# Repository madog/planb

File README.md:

# planb

Electrical and mechanical designs based on the Plan B powder printer (https://ytec3d.com/plan-b/)

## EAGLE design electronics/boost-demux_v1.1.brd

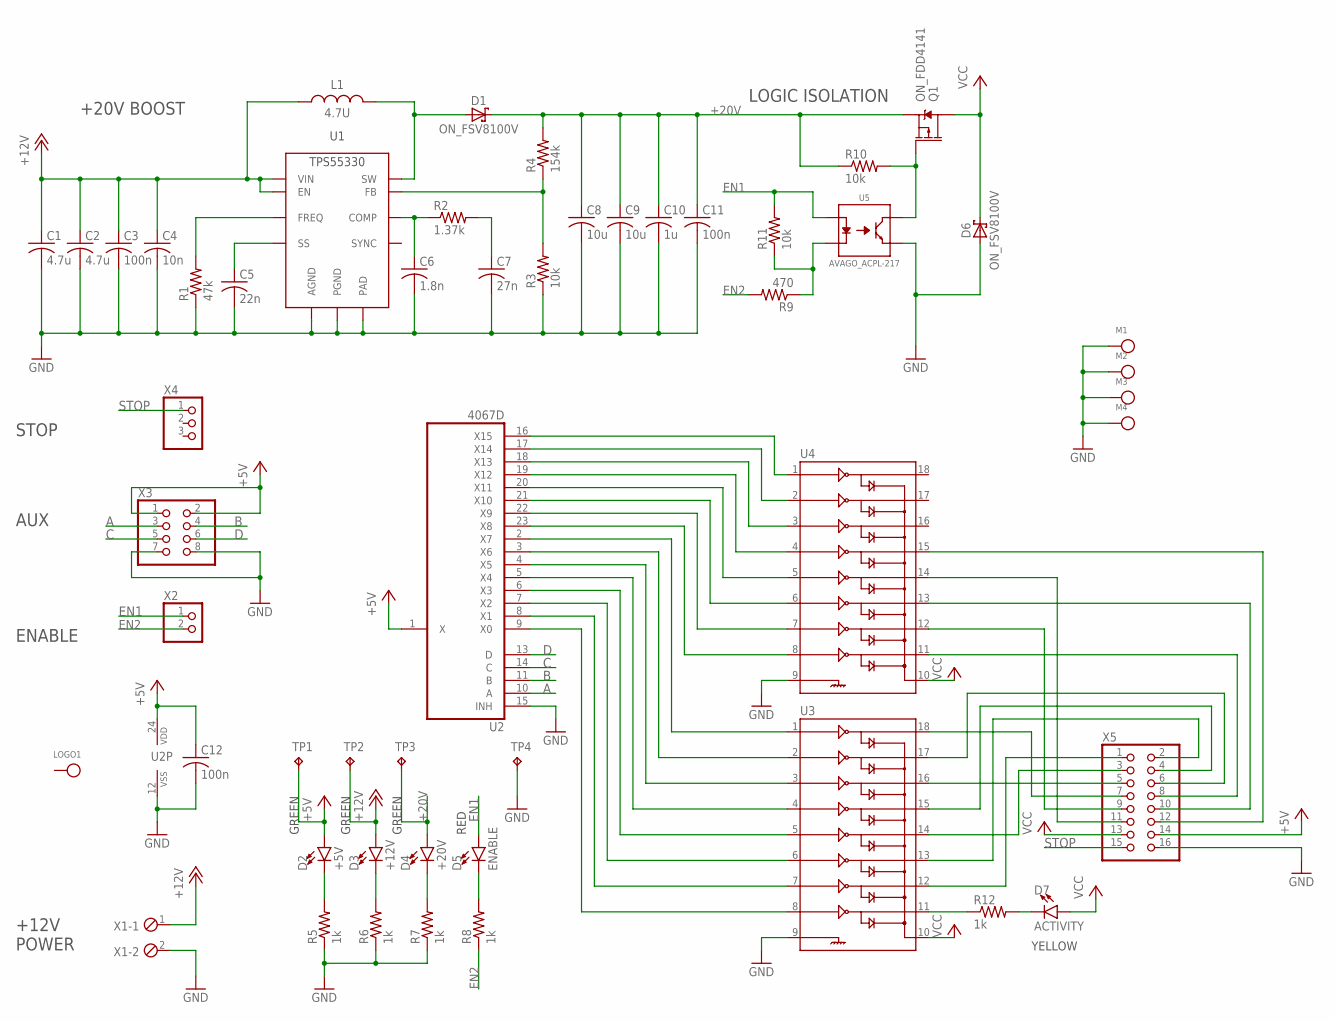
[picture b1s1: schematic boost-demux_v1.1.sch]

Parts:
C1, C2: 4.7u; C1206
C3, C11, C12: 100n; C1206
C4: 10n; C1206
C5: 22n; C1206
C6: 1.8n; C0805
C7: 27n; C0805
C8, C9: 10u; C1206
C10: 1u; C1206
D1, D6: ON_FSV8100V; TO-277-3
D2: +5V; LED_5MM
D3: +12V; LED_5MM
D4: +20V; LED_5MM
D5: ENABLE; LED_5MM
D7: ACTIVITY; LED_5MM
L1: 4.7U; 4440
LOGO1: MADOG
M1, M2, M3, M4: 6-32_MOUNT
Q1: ON_FDD4141; TO-252-3
R1: 47k; R1206
R2: 1.37k; R0805
R3, R10, R11: 10k; R0805
R4: 154k; R0805
R5, R6, R7, R8, R12: 1k; R1206
R9: 470; R1206
TP1, TP2, TP3, TP4: TPB1,27; B1,27
U1: TI_TPS55330; S-PWQFN-N16
U2: 4067D; SO24W
U3, U4: ULN2803SOICW; SO18L
U5: AVAGO_ACPL-217; SOIC-4
X1: MPT2; 2POL254
X2: PINHD-1X2/90; 1X02/90
X3: PINHD-2X4/90; 2X04/90
X4: PINHD-1X3/90; 1X03/90
X5: PINHD-2X8; 2X08

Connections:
+5V: C12.1, D2.A, TP1.TP, U2.1 (X), U2.24 (VDD), X3.1, X3.2, X5.14
+12V: C1.1, C2.1, C3.1, C4.1, D3.A, L1.1, TP2.TP, U1.2 (VIN), U1.3 (EN), X1.1
+20V: C8.1, C9.1, C10.1, C11.1, D1.P$3 (C), D4.A, Q1.P$3 (S), R4.2, R10.1, TP3.TP
A: U2.10 (A), X3.3
B: U2.11 (B), X3.4
C: U2.14 (C), X3.5
D: U2.13 (D), X3.6
EN1: D5.A, R11.2, U5.P$1, X2.1
EN2: R8.1, R9.2, X2.2
GND: C1.2, C2.2, C3.2, C4.2, C5.2, C6.2, C7.2, C8.2, C9.2, C10.2, C11.2, C12.2, D6.P$1 (A), D6.P$2 (A), M1.P$1, M1.P$2, M1.P$3, M1.P$4, M1.P$5, M1.P$6, M1.P$7, M1.P$8, M1.P$9, M2.P$1, M2.P$2, M2.P$3, M2.P$4, M2.P$5, M2.P$6, M2.P$7, M2.P$8, M2.P$9, M3.P$1, M3.P$2, M3.P$3, M3.P$4, M3.P$5, M3.P$6, M3.P$7, M3.P$8, M3.P$9, M4.P$1, M4.P$2, M4.P$3, M4.P$4, M4.P$5, M4.P$6, M4.P$7, M4.P$8, M4.P$9, R1.1, R3.1, R5.1, R6.1, R7.1, TP4.TP, U1.6 (AGND), U1.11 (PGND), U1.12 (PGND), U1.13 (PGND), U1.PAD, U2.12 (VSS), U2.15 (INH), U3.9, U4.9, U5.P$3, X1.2, X3.7, X3.8, X5.16
unnamed: R1.2, U1.9 (FREQ)
unnamed: C5.1, U1.4 (SS)
unnamed: C6.1, R2.1, U1.7 (COMP)
unnamed: C7.1, R2.2
unnamed: R3.2, R4.1, U1.8 (FB)
unnamed: D2.K (C), R5.2
unnamed: D1.P$1 (A), D1.P$2 (A), L1.2, U1.1 (SW), U1.15 (SW), U1.16 (SW)
unnamed: D3.K (C), R6.2
unnamed: D4.K (C), R7.2
unnamed: D5.K (C), R8.2
unnamed: U2.9 (X0), U3.8
unnamed: R12.1, U3.11
unnamed: Q1.P$1 (G), R10.2, U5.P$4
unnamed: U3.12, X5.1
unnamed: U2.8 (X1), U3.7
unnamed: U2.7 (X2), U3.6
unnamed: U2.6 (X3), U3.5
unnamed: U3.13, X5.2
unnamed: R9.1, R11.1, U5.P$2
unnamed: U2.5 (X4), U3.4
unnamed: U2.4 (X5), U3.3
unnamed: U2.3 (X6), U3.2
unnamed: U2.2 (X7), U3.1
unnamed: U2.23 (X8), U4.8
unnamed: U2.22 (X9), U4.7
unnamed: U2.21 (X10), U4.6
unnamed: U2.20 (X11), U4.5
unnamed: U2.19 (X12), U4.4
unnamed: U2.18 (X13), U4.3
unnamed: U2.17 (X14), U4.2
unnamed: U2.16 (X15), U4.1
unnamed: U3.14, X5.3
unnamed: U3.15, X5.4
unnamed: U3.16, X5.5
unnamed: U3.17, X5.6
unnamed: U3.18, X5.7
unnamed: U4.11, X5.8
unnamed: U4.12, X5.9
unnamed: U4.13, X5.10
unnamed: U4.14, X5.11
unnamed: U4.15, X5.12
unnamed: D7.K (C), R12.2
STOP: X4.1, X5.15
VCC: D6.P$3 (C), D7.A, Q1.P$4 (D), U3.10, U4.10, X5.13

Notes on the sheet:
+12V POWER
AUX
+20V BOOST
LOGIC ISOLATION
ENABLE
STOP
GREEN
RED
YELLOW

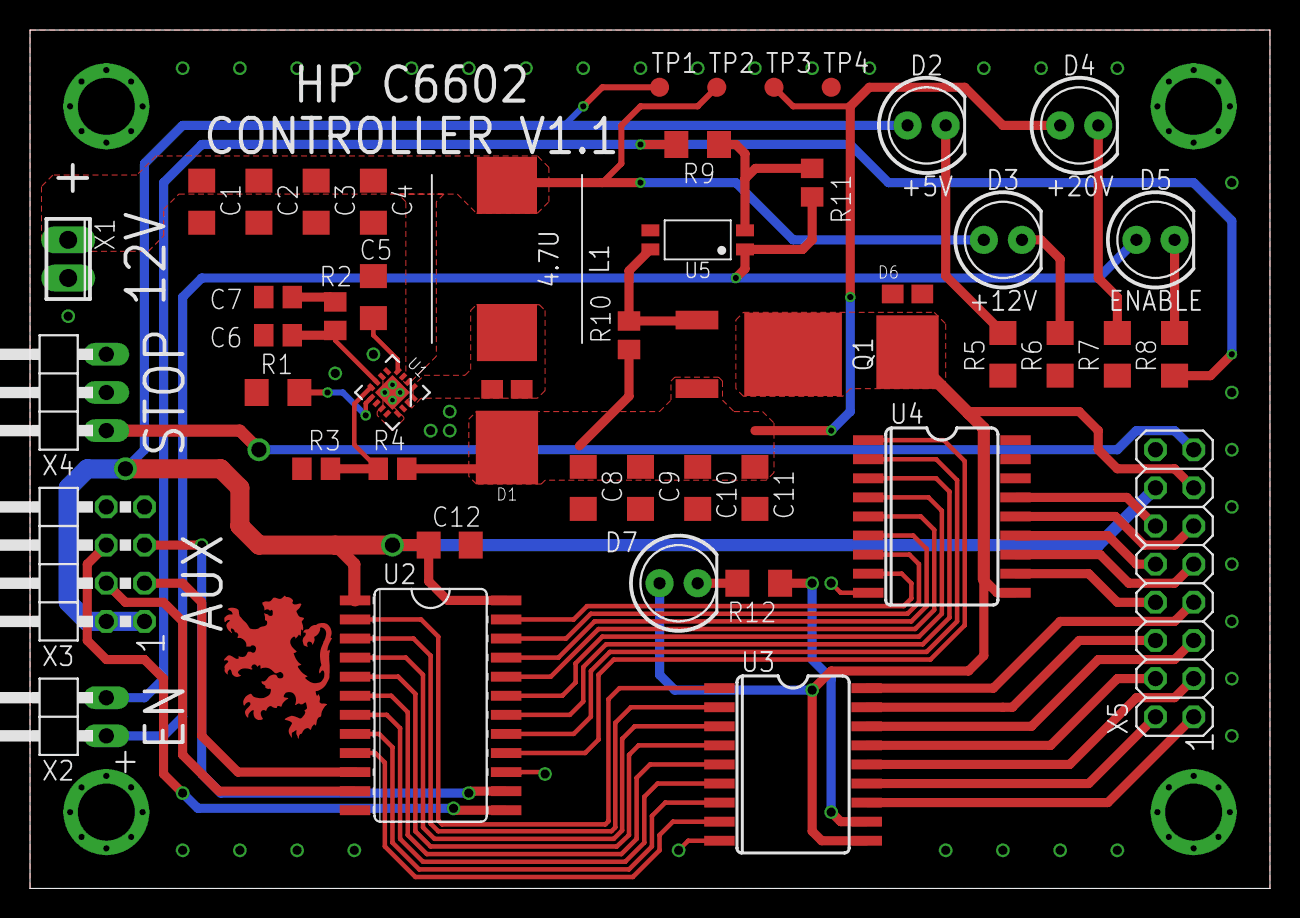
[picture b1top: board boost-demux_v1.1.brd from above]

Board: 2 copper layers, 82.5 x 57.1 mm, 52 parts (0 on the bottom side), 54 nets.

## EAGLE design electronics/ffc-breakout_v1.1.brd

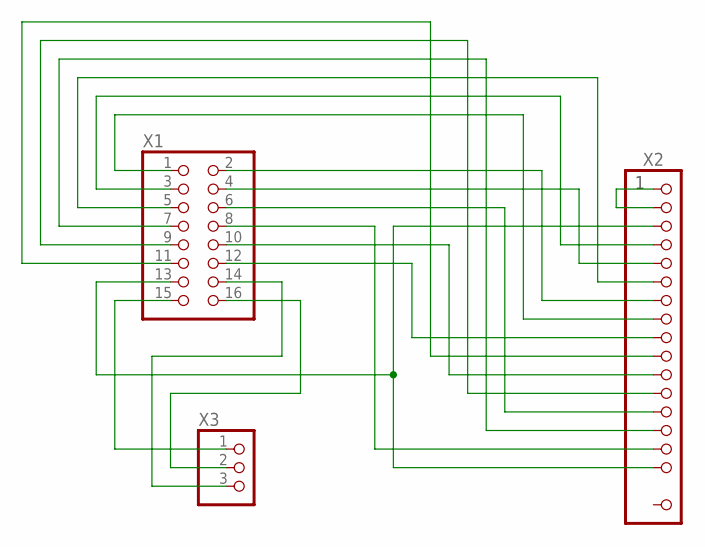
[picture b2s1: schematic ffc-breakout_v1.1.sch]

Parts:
X1: PINHD-2X8; 2X08
X2: AMP_SFW16R-2STE1LF
X3: PINHD-1X3/90; 1X03/90

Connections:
unnamed: X1.16, X3.2
unnamed: X1.15, X3.1
unnamed: X1.13, X2.P$3 (3), X2.P$16 (16)
unnamed: X1.14, X3.3
unnamed: X2.P$1 (1), X2.P$2 (2)
unnamed: X1.1, X2.P$8 (8)
unnamed: X1.2, X2.P$7 (7)
unnamed: X1.3, X2.P$4 (4)
unnamed: X1.4, X2.P$5 (5)
unnamed: X1.5, X2.P$6 (6)
unnamed: X1.6, X2.P$13 (13)
unnamed: X1.7, X2.P$14 (14)
unnamed: X1.8, X2.P$15 (15)
unnamed: X1.9, X2.P$12 (12)
unnamed: X1.10, X2.P$11 (11)
unnamed: X1.11, X2.P$10 (10)
unnamed: X1.12, X2.P$9 (9)

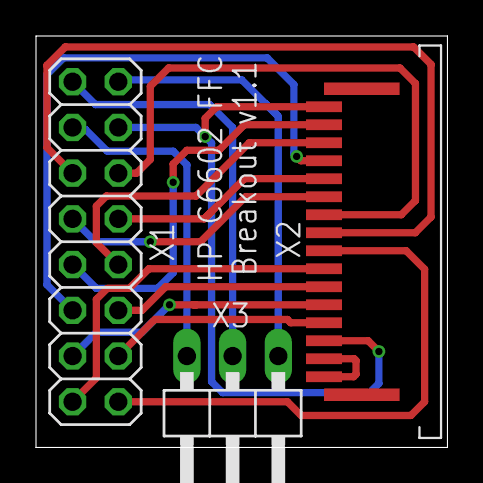
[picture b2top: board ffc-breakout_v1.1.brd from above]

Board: 2 copper layers, 22.9 x 22.9 mm, 3 parts (0 on the bottom side), 17 nets.

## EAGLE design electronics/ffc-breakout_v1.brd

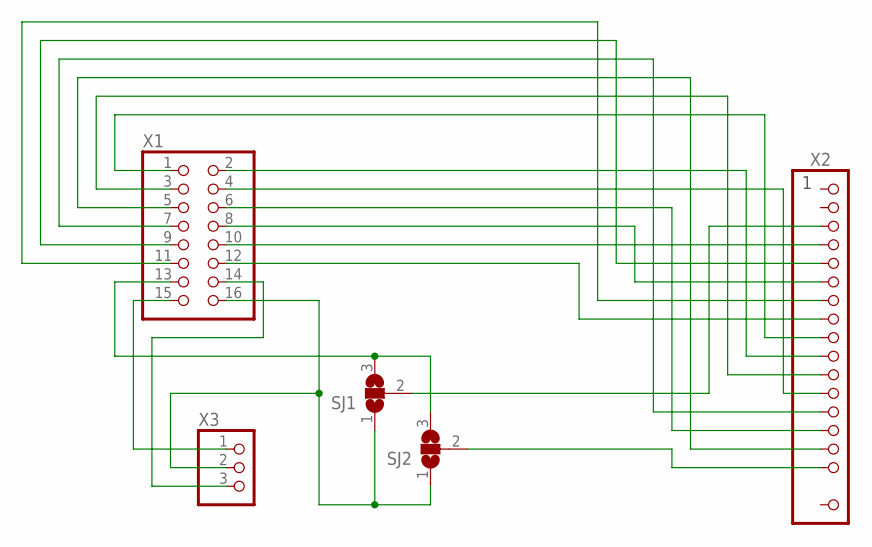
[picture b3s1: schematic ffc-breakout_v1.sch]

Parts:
SJ1, SJ2: SJ2W; SJ_2
X1: PINHD-2X8; 2X08
X2: AMP_SFW16R-2STE1LF
X3: PINHD-1X3/90; 1X03/90

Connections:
unnamed: SJ1.1, SJ2.1, X1.16, X3.2
unnamed: X1.15, X3.1
unnamed: SJ1.3, SJ2.3, X1.13
unnamed: X1.14, X3.3
unnamed: SJ1.2, X2.P$3 (3)
unnamed: X1.1, X2.P$9 (9)
unnamed: SJ2.2, X2.P$16 (16)
unnamed: X1.2, X2.P$10 (10)
unnamed: X1.3, X2.P$11 (11)
unnamed: X1.4, X2.P$12 (12)
unnamed: X1.5, X2.P$15 (15)
unnamed: X1.6, X2.P$14 (14)
unnamed: X1.7, X2.P$13 (13)
unnamed: X1.8, X2.P$6 (6)
unnamed: X1.9, X2.P$5 (5)
unnamed: X1.10, X2.P$4 (4)
unnamed: X1.11, X2.P$7 (7)
unnamed: X1.12, X2.P$8 (8)

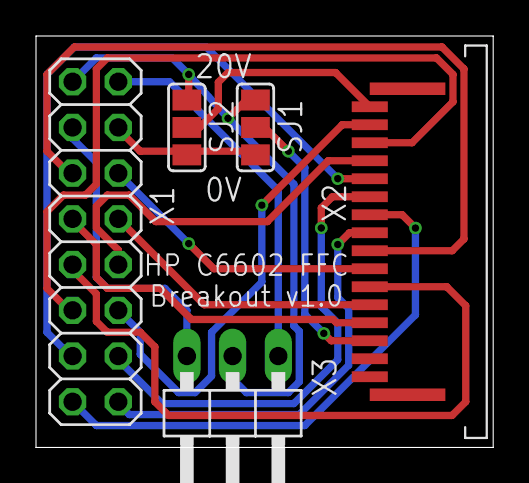
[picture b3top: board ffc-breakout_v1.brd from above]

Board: 2 copper layers, 25.4 x 22.9 mm, 5 parts (0 on the bottom side), 18 nets.

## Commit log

2017-08-27 Eagle project + schematic
2017-08-27 Add components lib + color palette
2017-08-27 Added Sparkfun libraries, OSHPark + DirtyPCBs files
2017-09-01 Components library - FFC connector (unfinished)
2017-09-02 Lib updates + boost-demux design
2017-09-03 Slight update to boost-demux schematic
2017-09-05 PCB draft less markup
2017-09-05 Added minor PCB markup
2017-09-06 Updates to boost-demux and FFC breakout
2017-09-06 FFC breakout autoroute
2017-09-06 FFC - much better autoroute + cleanup and markup
2017-09-06 DRC fixes
2017-09-06 BOM + minor FFC update
2017-09-08 Logos
2017-09-09 BOM updates and minor DRC fixes
2017-09-11 Rearrange + add mechanics and software files
2017-09-14 Removed Inventor files temporarily
2017-09-14 Updated all SW files to latest format
2017-09-14 Beginning of Inventor feature recognition
2017-09-14 Additional Inventor parts
2017-09-14 More parts + hardware
2017-09-14 More hardware
2017-09-15 Started sheet metal models
2017-09-15 Lots of parts
2017-09-15 Further parts
2017-09-17 Megatronics models
2017-09-17 Steppers
2017-09-17 Piston parts
2017-09-17 More piston parts
2017-09-18 Spreader parts +
2017-09-19 X-axis + Y-axis parts
2017-09-19 Subassemblies
2017-09-20 More subassembly
2017-09-22 Assemblies!
2017-09-25 Sheet metal mods
2017-09-25 Sheet metal drawings
2017-09-27 Hopper assy's
2017-09-27 More subassemblies + piston guide remodels
2017-09-28 Piston assy
2017-09-29 Finished subassys?
2017-10-03 Sheet metal updates + more assemblies
2017-10-03 Final subassemblies?
2017-10-05 Added STLs for 3D prints, moved Arduino source
2017-10-07 McMaster parts
2017-10-11 Parts list
2017-10-13 C6602 test program
2017-10-13 C6602 test draft
2017-10-13 Fixed test program bugs
2017-10-16 Test programs
2017-10-16 Pump test program update
2017-10-17 Draft PCB updates
2017-10-19 Minor PCB and parts list update
2017-10-23 Electronics v1.1 draft updates
2017-10-24 PCBs v1.1 final
2017-10-27 Main assy
2017-11-11 Stepper screw update
2017-11-14 Main assy updates
2017-11-14 Sheet metal assy - screws
2017-11-17 Material/appearance updates
2017-11-18 Main assy - spreader updates
2017-11-21 Belts and shaft couplers
2017-11-21 Spreader belt
2017-11-21 Removed Solidworks files, moved Inventor model to main directory
2017-11-25 Minor part updates
2017-12-08 Minor assembly updates
2017-12-31 Software updates + purge program
2017-12-31 Updated purge program
2017-12-31 Fix purge volume + add reset
2018-04-14 Added feed piston heat Started new UI design

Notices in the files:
parts and their libraries:
SparkFun-LED: Licensing: Creative Commons ShareAlike 4.0 International - https://creativecommons.org/licenses/by-sa/4.0
